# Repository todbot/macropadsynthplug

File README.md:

# MacroPadSynthPlug!

Turn MacroPad RP2040's StemmaQT port into Audio Out + MIDI In

Demo video on Youtube:

## What is this?

The [Adafruit MacroPad RP2040](https://learn.adafruit.com/adafruit-macropad-rp2040/overview)
is really fun and could be a great musical instrument,
with its 12 keys, rotary encoder, OLED display, RP2040 chip, and 8MB of flash storage.

If it only had a way to get MIDI into it and Audio out of it!
Well now you can, with MacroPadSynthPlug!

MacroPadSynthPlug is a small board that plugs into a StemmaQT / Qwiic port
and gives you [TRS-A MIDI In](https://minimidi.world/) and Audio line out.
It's not I2C, but is using those pins. 

The MacroPad RP2040 can now be a stand-alone MIDI synth!

Examples provided for both [CircuitPython](https://circuitpython.org/) and [Arduino](https://arduino-pico.readthedocs.io/en/latest/):

* __drum_machine__ - CircuitPython-based drum sequencer ([demo1](https://youtu.be/jMKC_18M17U),[demo2](https://youtu.be/bJwyUjxc6VM) )
* __dronesynth__ - Arduino Mozzi 12-oscillator drone synth ([demo](https://youtu.be/kLwP-vyvtLM))
* __remixer__ - CircuitPython-based song remixer ([source](https://github.com/todbot/macropadsynthplug/tree/main/circuitpython/remixer))
* __monosynth1__ - Arduino Mozzi 2-oscillator bass monosynth w/ resonant low-pass filter ([source](https://github.com/todbot/macropadsynthplug/tree/main/arduino/monosynth1))

## How?

The [Raspberry Pi RP2040 chip](https://www.raspberrypi.com/documentation/microcontrollers/rp2040.html)
on the MacroPad RP2040 is amazingly configurable.

Normally a port like the StemmaQT I2C port would only be usable as an I2C bus. 
With the MacroPad RP2040, the two StemmaQT pins have the possible functionality:

* MacroPad RP2040 StemmaQT SDA -- GP20 - UART1 TX - PWM2B
* MacroPad RP2040 StemmaQT SCL -- GP21 - UART1 RX - PWM2A

MacroPadSynthPlug is a simple combination of two circuits:

* For MIDI in: StemmaQT SCL has an optoisolator circuit and TRS MIDI In jack

* For PWM Audio Out: StemmaQT SDA has a PWM filtering circuit and Audio Out jack

This is an "abuse" of the StemmaQT port, as it's meant only for I2C devices.
But it's safe, will not damage other StemmaQT devices,
but it does mean you "lose" the StemmaQT port for its normal use with I2C.

## Does this work for other boards with StemmaQT?

Short answer: Yes, with caveats

* For audio out, any board that can do PWM on StemmaQT SDA can use the
  Audio Out side of MacroPadSynthPlug

* For MIDI In, any boards that can do UART In on StemmaQT SCL can do TRS MIDI input. 
  A "software serial" for TRS MIDI In may work, and of course USB MIDI In will 
  always work

This makes this list of boards this works with kinda small. 

### Tested boards:

* [Adafruit MacroPad RP2040](https://learn.adafruit.com/adafruit-macropad-rp2040)

* [Adadfruit KB2040 "Keeboar"](https://learn.adafruit.com/adafruit-kb2040)

* [Adafruit QTPy RP2040](https://learn.adafruit.com/adafruit-qt-py-2040) 
  * with a PIO-based UART libary like [`SerialPIO`](https://arduino-pico.readthedocs.io/en/latest/piouart.html) or [`adafruit_pio_uart`](https://github.com/adafruit/Adafruit_CircuitPython_PIO_UART)
  * as an example, see [qtpy_mpsp_synth](./circuitpython/qtpy_mpsp_synth/code.py)

* Raspberry Pi Pico or Pico 2 
  * with a [StemmaQT](https://www.adafruit.com/product/4209) / [Qwiic](https://www.sparkfun.com/flexible-qwiic-cable-breadboard-jumper-4-pin.html) breadboard jumper cable

## Why?

Seems like fun?  I have built many little hardware synths, like:

- [PicoStepSeq](https://github.com/todbot/picostepseq)
- [picotouchsynth](https://github.com/todbot/picotouchsynth)
- [plinkykeeb](https://github.com/todbot/plinkykeeb)
- [seeknobs](https://github.com/todbot/seeknobs)

and wanted the MacroPad RP2040 to join in the fun.

## Are these for sale?

Yes! [Get one now at Tindie!](https://www.tindie.com/products/todbot/macropadsynthplug-turn-rp2040-into-a-synth/)

## Action shots

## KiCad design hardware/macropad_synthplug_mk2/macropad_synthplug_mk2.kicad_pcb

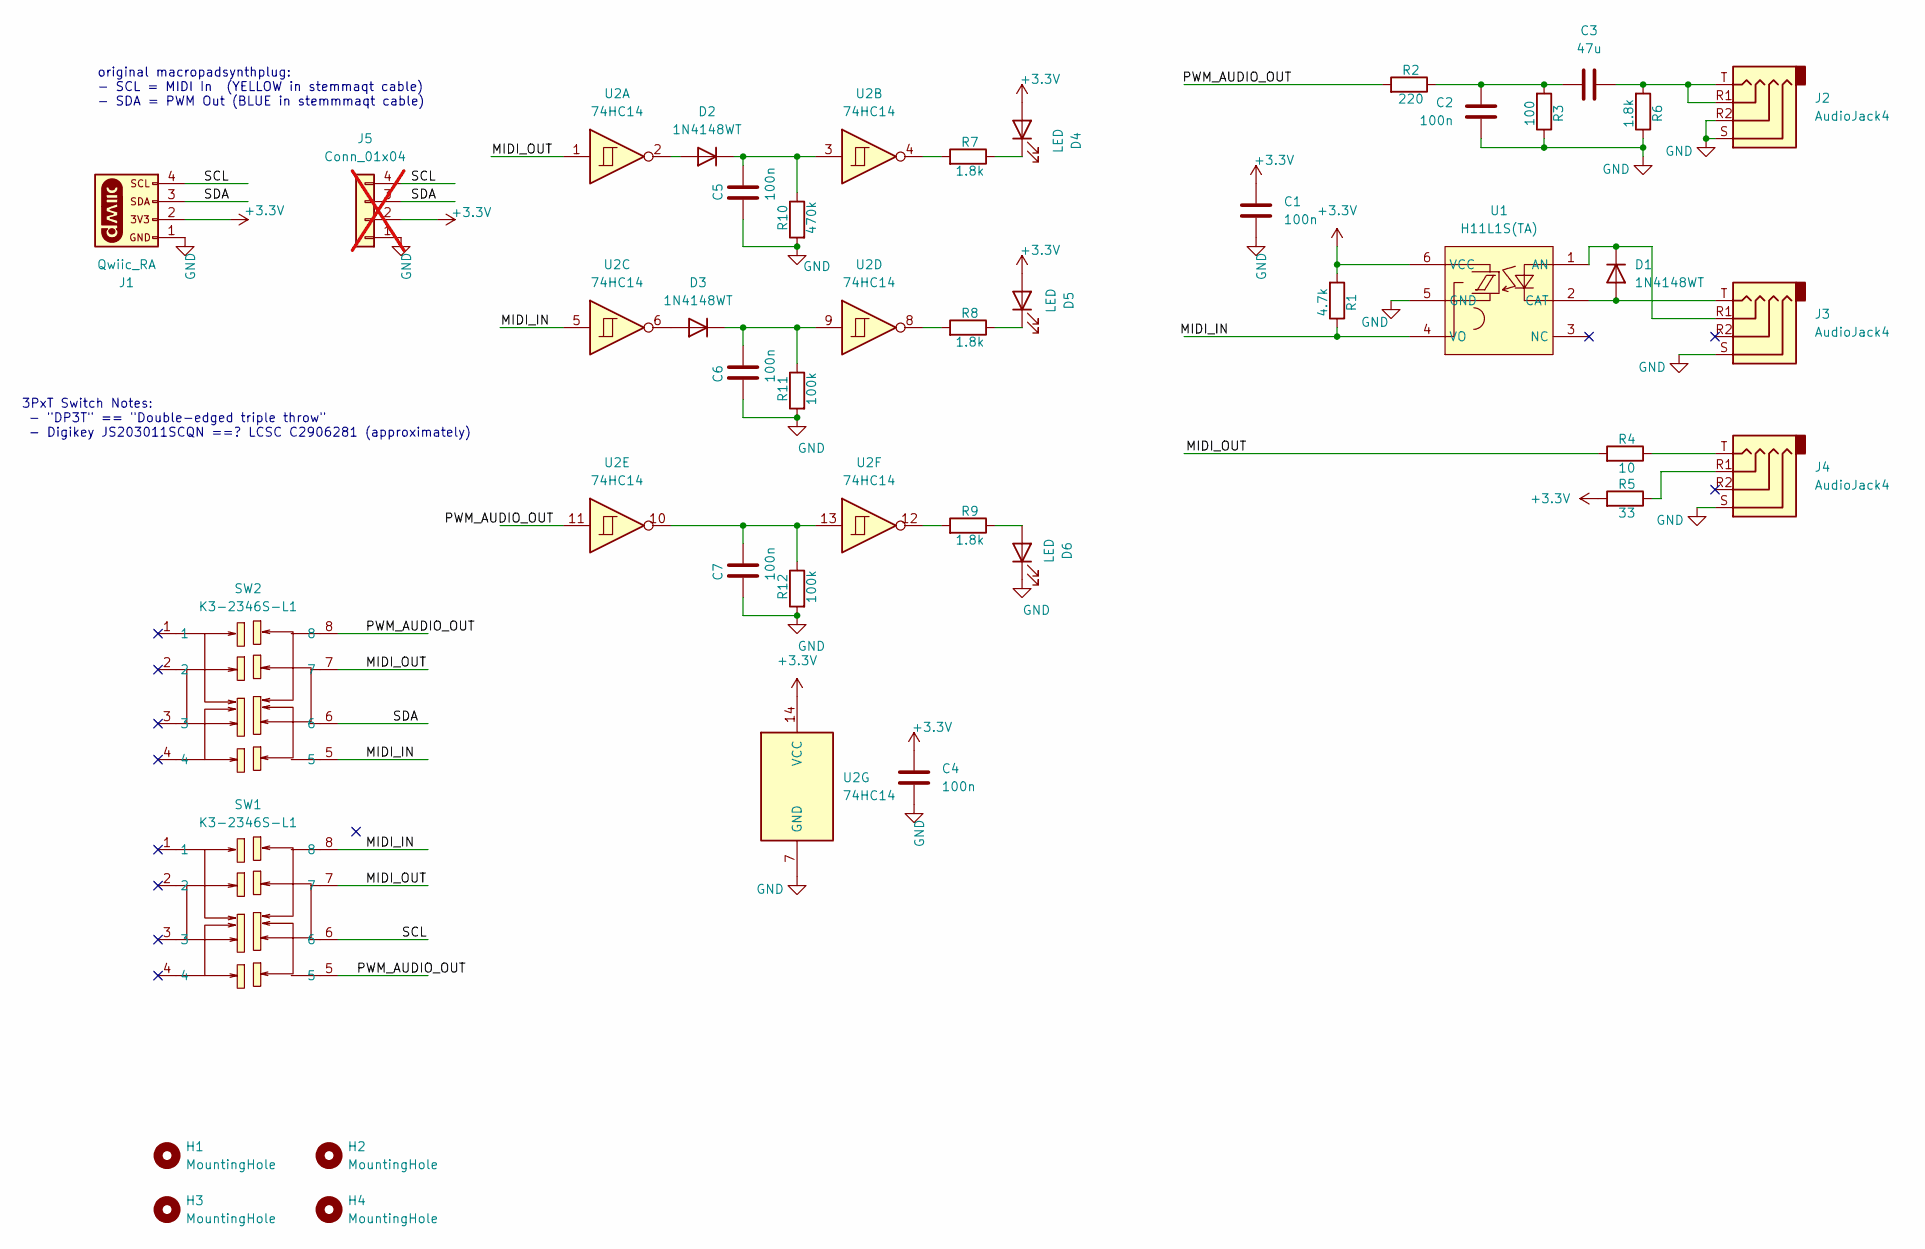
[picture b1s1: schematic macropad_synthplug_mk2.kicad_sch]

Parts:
C1, C2, C4, C5, C6, C7: 100n; C_0603_1608Metric
C3: 47u; C_0603_1608Metric
D1, D2, D3: 1N4148WT; D_SOD-123F; LCSC Part C64898
D4, D5, D6: LED; LED_0603_1608Metric
H1, H2, H3, H4: MountingHole; MountingHole_2.5mm
J1: Qwiic_RA; JST_SMD_1.0mm-4_RA; LCSC Part C2845363
J2, J3: AudioJack4; Jack_3.5mm_PJ320D_Horizontal; LCSC Part C431535
J4: AudioJack4; Jack_3.5mm_PJ320D_Horizontal; LCSC C431535
J5: Conn_01x04; PinHeader_1x04_P2.54mm_Vertical; not fitted
R1: 4.7k; R_0603_1608Metric
R2: 220; R_0603_1608Metric
R3: 100; R_0603_1608Metric
R4: 10; R_0603_1608Metric
R5: 33; R_0603_1608Metric
R6, R7, R8, R9: 1.8k; R_0603_1608Metric
R10: 470k; R_0603_1608Metric
R11, R12: 100k; R_0603_1608Metric
SW1, SW2: K3-2346S-L1; SW-SMD_K3-2346S-L1; LCSC Part C707355
U1: H11L1S(TA); SMD-6_L7.3-W6.5-P2.54-LS10.2-BL; LCSC Part C78589
U2: 74HC14; SOIC-14_3.9x8.7mm_P1.27mm

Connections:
+3.3V: C1.1, C4.1, D4.2 (A), D5.2 (A), J1.2, J5.2, R1.2, R5.2, U1.6 (VCC), U2.14 (VCC)
/MIDI_IN: R1.1, SW1.8, SW2.5, U1.4 (VO), U2.5
/MIDI_OUT: R4.2, SW1.7, SW2.7, U2.1
/PWM_AUDIO_OUT: R2.2, SW1.5, SW2.8, U2.11
/SCL: J1.4, J5.4, SW1.6
/SDA: J1.3, J5.3, SW2.6
GND: C1.2, C2.2, C4.2, C5.2, C6.2, C7.2, D6.1 (K), J1.1, J2.R2, J2.S, J3.S, J4.S, J5.1, R3.1, R6.1, R10.2, R11.2, R12.2, U1.5 (GND), U2.7 (GND)
unnamed: C2.1, C3.2, R2.1, R3.2
unnamed: C3.1, J2.R1, J2.T, R6.2
unnamed: C7.1, R12.1, U2.10, U2.13
unnamed: D1.2 (A), J3.T, U1.2 (CAT)
unnamed: D1.1 (K), J3.R1, U1.1 (AN)
unnamed: D2.2 (A), U2.2
unnamed: C5.1, D2.1 (K), R10.1, U2.3
unnamed: D3.2 (A), U2.6
unnamed: C6.1, D3.1 (K), R11.1, U2.9
unnamed: D4.1 (K), R7.1
unnamed: D5.1 (K), R8.1
unnamed: D6.2 (A), R9.1
unnamed: J4.R1, R5.1
unnamed: J4.T, R4.1
unnamed: R7.2, U2.4
unnamed: R8.2, U2.8
unnamed: R9.2, U2.12

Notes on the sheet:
original macropadsynthplug: - SCL = MIDI In (YELLOW in stemmaqt cable) - SDA = PWM Out (BLUE in stemmmaqt cable)
3PxT Switch Notes: - "DP3T" == "Double-edged triple throw" - Digikey JS203011SCQN ==? LCSC C2906281 (approximately)

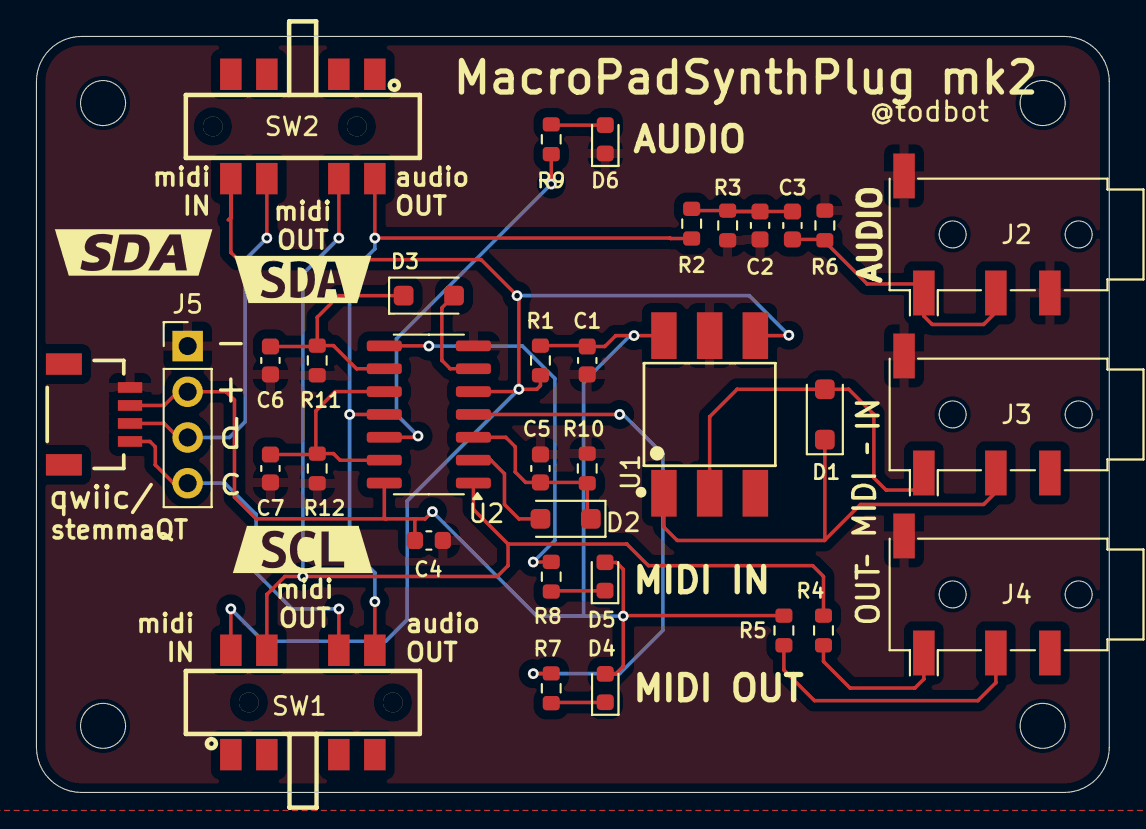
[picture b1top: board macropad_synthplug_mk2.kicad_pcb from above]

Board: 2 copper layers, 59.6 x 42.0 mm, 41 parts (0 on the bottom side), 24 nets.

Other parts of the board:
kibuzzard-6721CAF2: G***; kibuzzard-6721CAF2
kibuzzard-6721CB0B: G***; kibuzzard-6721CB0B
kibuzzard-6721CC38: G***; kibuzzard-6721CC38

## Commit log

2022-12-15 submit!
2022-12-16 added some hardware test sketches
2022-12-31 add usb midi input to drummachine
2023-01-01 sync up with local
2023-01-01 add async attempt
2023-01-01 allow use of built-in tiny spkr
2023-01-01 added track mutes
2023-01-01 prelim pattern changing
2023-01-01 change display layout to be more usable
2023-01-01 cleanup
2023-01-01 sigh ticks overflow, why cant you be like arduino
2023-01-01 add docs images
2023-01-02 added sch pdf
2023-01-02 add ability to select multiple kits
2023-01-02 fix pattern for multi-kit setup
2023-01-02 display layout fix
2023-01-03 preparing for being abel to save patterns
2023-01-03 added kit2
2023-01-03 fix kit1_tac, prepare for save/load patterns
2023-01-03 mention about code_async, add boot.py for saving sequences
2023-01-05 add a kind of quantizing
2023-01-05 add patterns save/load first cut
2023-01-05 long version of board
2023-01-08 submit long version to fab
2023-01-08 cleanup arduino hardware test 1
2023-01-11 rework pattern storage, now using bit positions
2023-01-11 more UI improvements to drum_machine
2023-01-11 go back to arrays for sequence, but store as binary string
2023-01-12 save pattern cleanup
2023-01-12 clean up drumpatterns
2023-01-13 invert patterns data structure to make it easier to read and design demo patterns
2023-01-14 copy pattern and save pattern
2023-01-16 midi receive uses todbot_smolishmidi now
2023-01-16 crap
2023-01-21 get the trrs pinout right for realsies yeesh
2023-01-21 arduino tests rename
2023-01-21 sorta working hagiwo_additive_vco
2023-01-21 additive vco knob works better
2023-01-23 add macropadsynthplug verison of dronesynth
2023-01-23 more dronesynth
2023-01-23 more dronesynth work, pretty neat now
2023-01-24 dronesynth first midi
2023-01-24 dronesynth pretty fun now
2023-01-27 monosynth1 mostly works
2023-02-02 oops on additive_vco_synth
2023-02-03 tindie link
2023-02-12 oops forgot drum_display.py
2023-03-02 add autopunkconsole
2023-03-09 cleanup silkscreen, send to fab
2023-03-19 circuitpython drum_machine: how did I miss this
2023-10-23 arduino/dronesynth, fix serial midi input, issue #1
2023-10-23 arduino/dronesynth: handle noteon/noteoff better
2023-10-23 arduino/monosynth1: fix serial MIDI in
2024-09-29 clarify what StemmaQT pins do what on MacroPad RP2040
2024-10-22 new synthplug incoming
2024-10-22 sch reorg
2024-10-22 mk2 size and silkscreen update
2024-10-22 mk2 routing fixes
2024-10-30 silkscreen for mk2
2024-11-23 mk2 silkscreen update
2025-05-16 readme updates
2025-05-16 qtpy rp2040 example
